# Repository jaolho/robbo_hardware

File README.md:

# CLONE THE REPOSITORY BY CLICKING THE CLONE BUTTON IN THE UPPER RIGHT SIDE OF THE PAGE - THE ONE WITH A DOWN ARROW. #

# README #

This README would normally document whatever steps are necessary to get your application up and running.

### What is this repository for? ###

* Quick summary
* Version
* [Learn Markdown](https://bitbucket.org/tutorials/markdowndemo)

### How do I get set up? ###

* Summary of set up
* Configuration
* Dependencies
* Database configuration
* How to run tests
* Deployment instructions

### Contribution guidelines ###

* Writing tests
* Code review
* Other guidelines

### Who do I talk to? ###

* Repo owner or admin
* Other community or team contact

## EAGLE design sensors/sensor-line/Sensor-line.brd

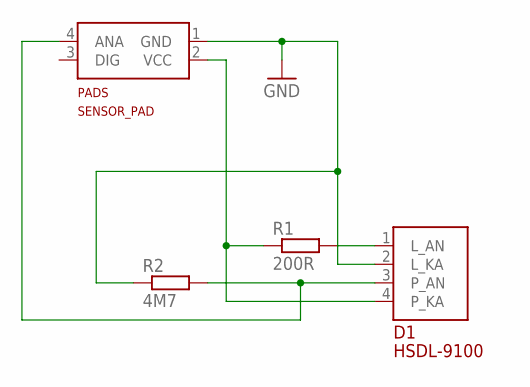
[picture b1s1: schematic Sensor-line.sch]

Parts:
D1: HSDL-9100; MPN HSDL-9100-021
PADS: SENSOR_PAD
R1: 200R; R1206; MPN ERJ8ENF2000V
R2: 4M7; R0805; MPN ASC0805-4M7FT5

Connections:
GND: D1.2 (L_KA), PADS.1 (GND), R2.1
unnamed: D1.1 (L_AN), R1.2
unnamed: D1.3 (P_AN), PADS.4 (ANA), R2.2
unnamed: D1.4 (P_KA), PADS.2 (VCC), R1.1

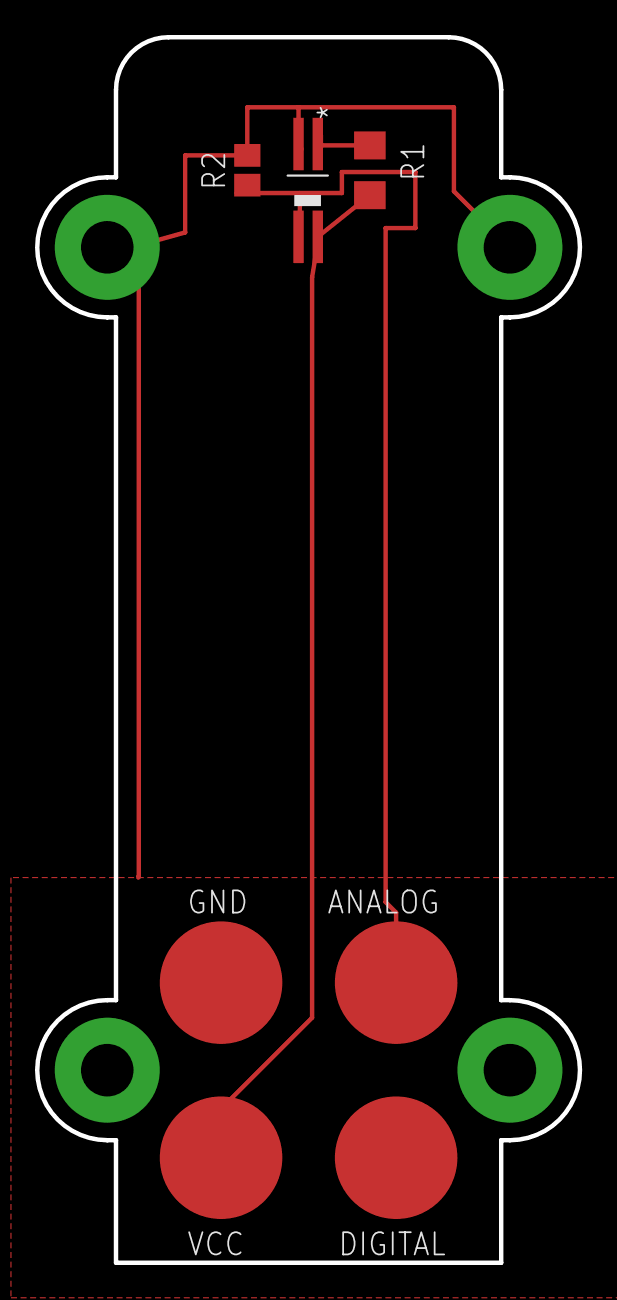
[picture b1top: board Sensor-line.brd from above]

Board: 2 copper layers, 31.0 x 70.0 mm, 4 parts (1 on the bottom side), 4 nets.

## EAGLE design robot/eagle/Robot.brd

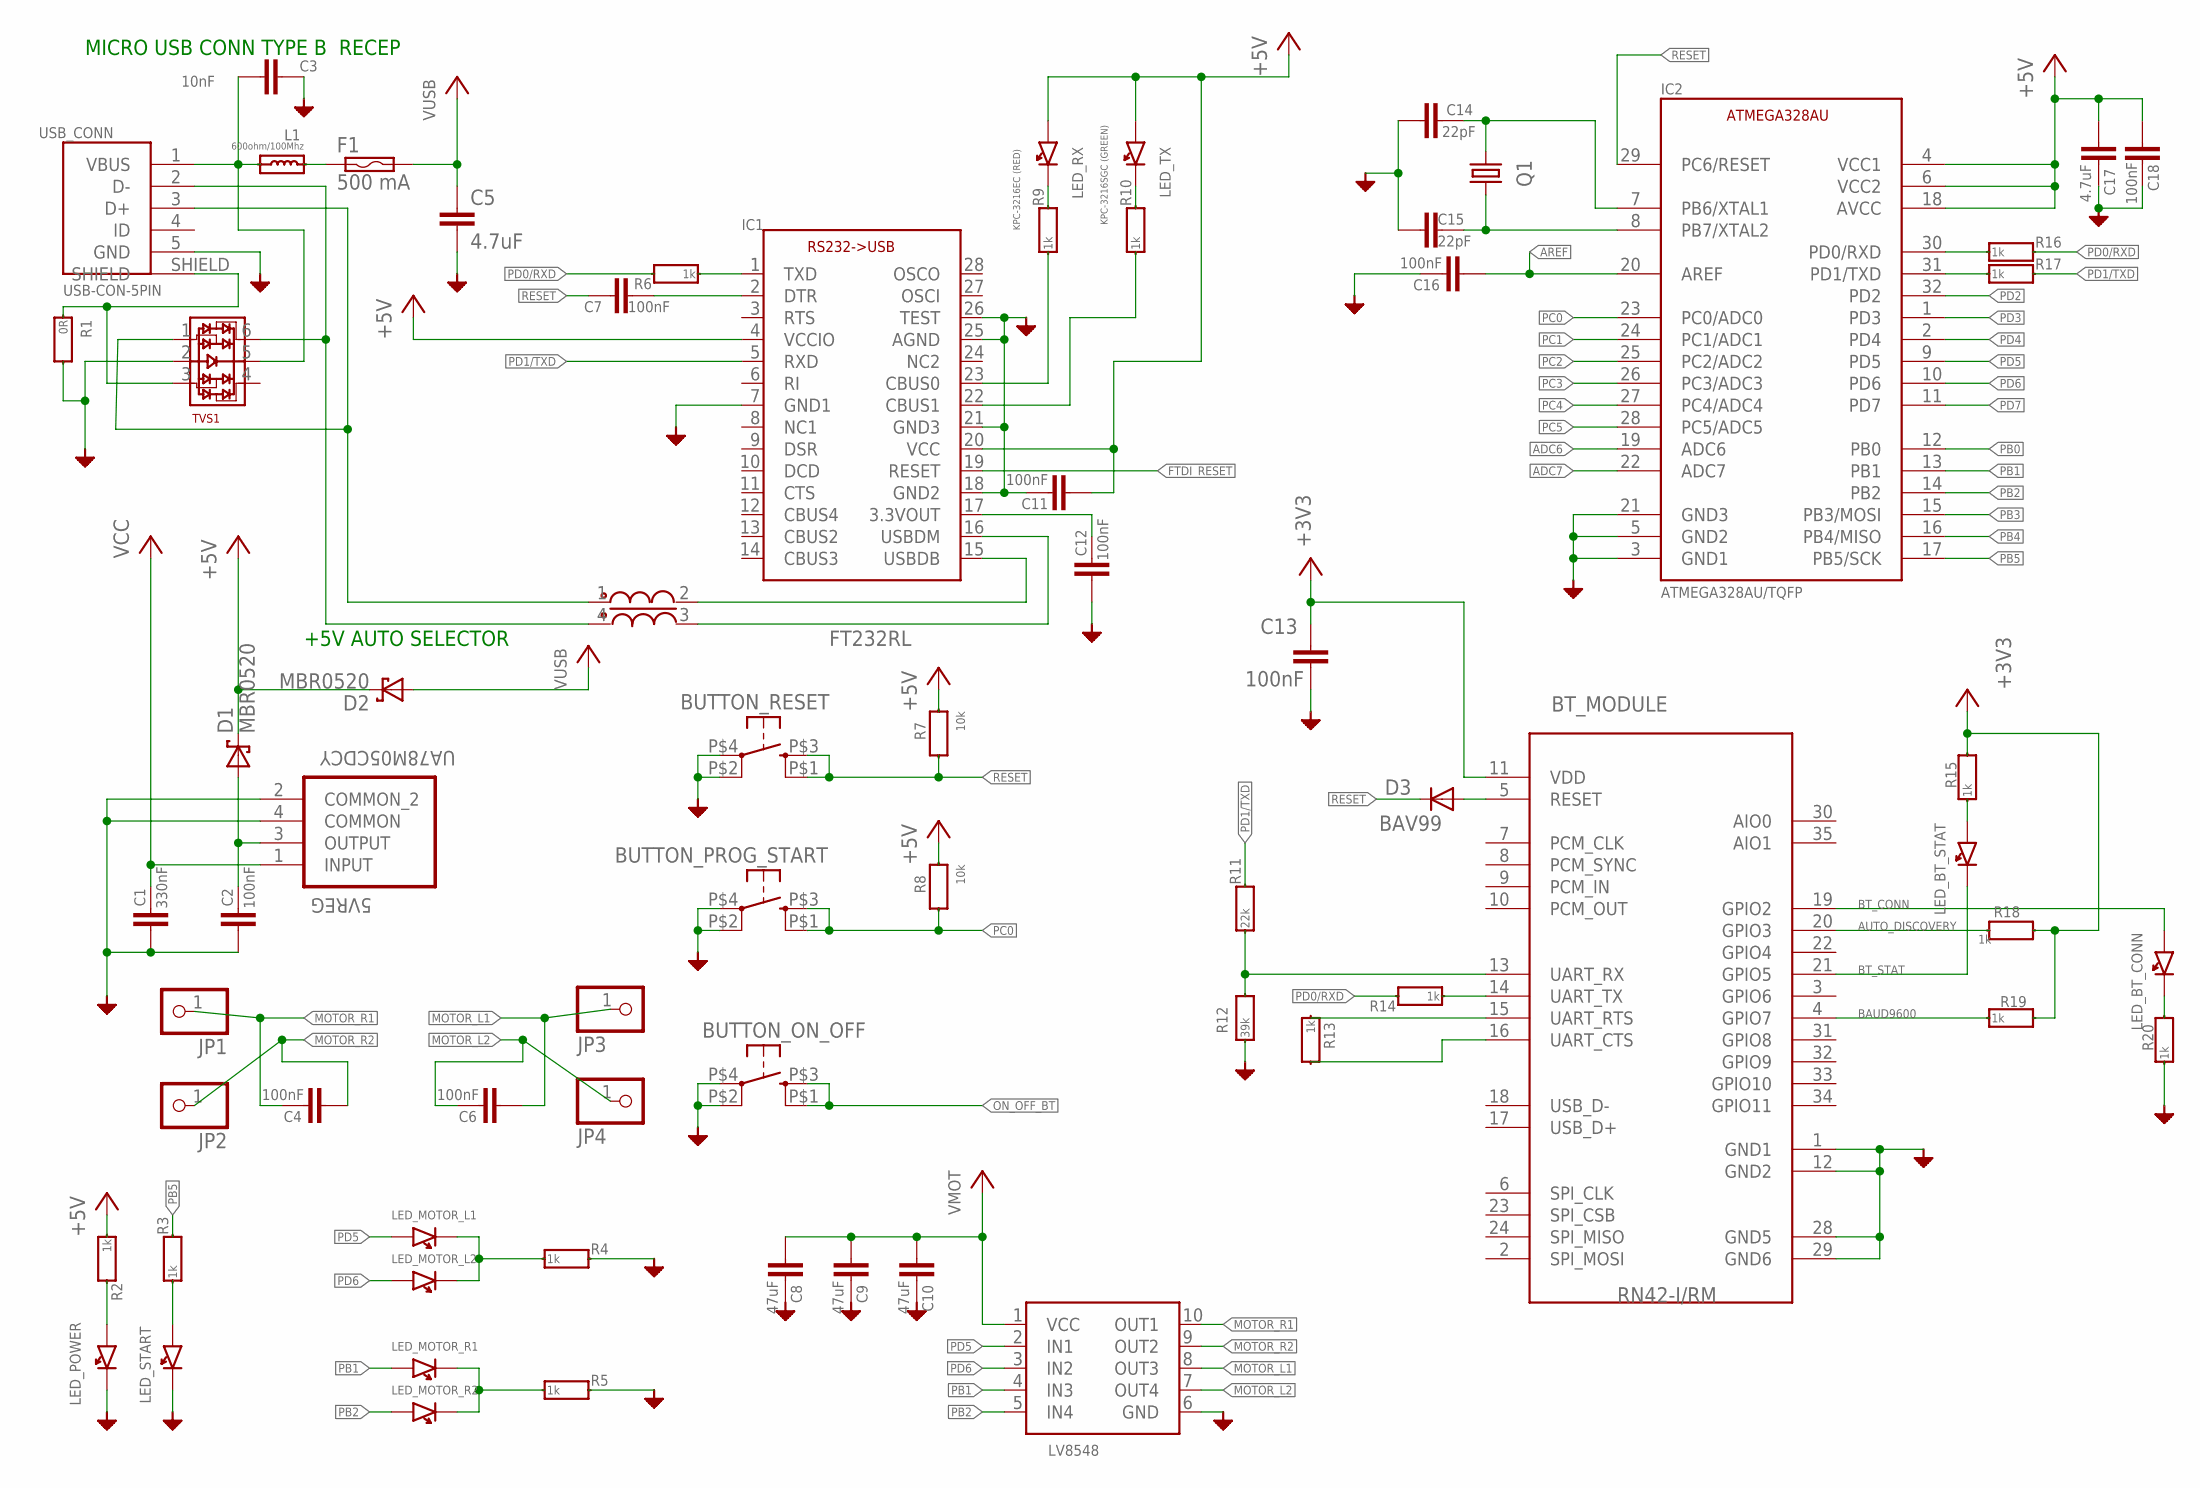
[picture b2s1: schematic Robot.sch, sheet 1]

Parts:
5VREG: UA78M05CDCY; SOT230P700X180-4N
BT_MODULE: RN42-I/RM; RN42; MPN RN42-I/RM
BUTTON_ON_OFF: KSC921J; TACT_SWITCH_4_PIN; MPN KSC921J LFS
BUTTON_PROG_START: KSC921J; TACT_SWITCH_4_PIN; MPN KSC921J LFS
BUTTON_RESET: KSC921J; TACT_SWITCH_4_PIN; MPN KSC921J LFS
C1: 330nF; C0805; MPN 08053C334KAT2A
C2, C4, C6, C7, C11, C12, C13, C16, C18: 100nF; C0805; MPN 08055C104KAT2A
C3: 10nF; C0805; MPN MC0805B103K500CT
C5, C17: 4.7uF; C0805; MPN GRM21BR61E475KA12L
C8, C9, C10: 47uF; C1210; MPN GRM32EC81C476KE15L
C14, C15: 22pF; C0805; MPN CC0805JRNPO9BN220
D1, D2: MBR0520; SOD123; MPN MBR0520L
D3: BAV99; SOT23; MPN BAV99
F1: 500 mA; PT1206; MPN NANOSMDC050F/13.2-2
IC1: FT232RL; SSOP28; MPN FT232RL-REEL
IC2: ATMEGA328AU/TQFP; TQFP32-08; MPN ATMEGA328P-AU
JP1, JP2, JP3, JP4: 1X01 PIN; 1X01; MPN 61300111121
L1: 600ohm/100Mhz; R0603; MPN 742792651
LED_BT_CONN: KPC-3216SGC; LED3216_PAC; MPN KPC-3216SGC
LED_BT_STAT: KPC-3216SGC; LED3216_PAC; MPN KPC-3216SGC
LED_MOTOR_L1: APT3216QBC/D (BLUE); LED3216_PAC; MOUSER_PART_NO 604-APT3216QBC/D
LED_MOTOR_L2: KPC-3216YC; LED3216_PAC; MPN KPC-3216YC
LED_MOTOR_R1: APT3216QBC/D (BLUE); LED3216_PAC; MOUSER_PART_NO 604-APT3216QBC/D
LED_MOTOR_R2: KPC-3216YC; LED3216_PAC; MPN KPC-3216YC
LED_POWER: KPC-3216SGC (GREEN); LED3216_PAC; MPN KPC-3216SGC
LED_RX: KPC-3216EC (RED); LED3216_PAC; MPN KPC-3216EC
LED_START: KPC-3216SGC; LED3216_PAC; MPN KPC-3216SGC
LED_TX: KPC-3216SGC (GREEN); LED3216_PAC; MPN KPC-3216SGC
MOTOR_CONTROLLER: LV8548; MPN LV8548MC-AH
Q1: 16MHz; SM49; MPN LFXTAL003237
R1: 0R; R0805; MPN MC01W08050R
R2, R3, R4, R5, R6, R9, R10, R13, R14, R15, R16, R17, R18, R19, R20: 1k; R0805; MPN CRCW08051K00FKTA
R7, R8: 10k; R0805; MPN RC0805FR-0710KL
R11: 22k; R0805; MPN WCR0805-22KFI
R12: 39k; R0805; MPN WCR0805-39KFI
TVS1: PRTR5V0U4Y; SOT363; MPN PRTR5V0U4Y,125
USB_CONN: USB-CON-5PIN; USB-MICRO-MOLEX-105017-0001_V2; MPN 105017-0001
USB_FILTER: SRF3216A; MPN SRF3216A-900Y

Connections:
+3V3: BT_MODULE.11 (VDD), C13.1, R15.2, R18.2, R19.2; also elsewhere on the board
+5V: C11.2, C17.2, C18.2, D1.1 (K), D2.1 (K), IC1.4 (VCCIO), IC1.20 (VCC), IC2.4 (VCC1), IC2.6 (VCC2), IC2.18 (AVCC), LED_RX.1, LED_TX.1, R2.1, R7.2, R8.2; also elsewhere on the board
ADC6: IC2.19 (ADC6); also elsewhere on the board
ADC7: IC2.22 (ADC7); also elsewhere on the board
AREF: C16.2, IC2.20 (AREF); also elsewhere on the board
AUTO_DISCOVERY: BT_MODULE.20 (GPIO3), R18.1
BAUD9600: BT_MODULE.4 (GPIO7), R19.1
BT_CONN: BT_MODULE.19 (GPIO2), LED_BT_CONN.1
BT_STAT: BT_MODULE.21 (GPIO5), LED_BT_STAT.2
FTDI_RESET: IC1.19 (RESET); also elsewhere on the board
GND: 5VREG.2 (COMMON_2), 5VREG.4 (COMMON), BT_MODULE.1 (GND1), BT_MODULE.12 (GND2), BT_MODULE.28 (GND5), BT_MODULE.29 (GND6), BUTTON_ON_OFF.P$2 (2), BUTTON_ON_OFF.P$4 (1), BUTTON_PROG_START.P$2 (2), BUTTON_PROG_START.P$4 (1), BUTTON_RESET.P$2 (2), BUTTON_RESET.P$4 (1), C1.2, C2.2, C3.1, C5.2, C8.1, C9.1, C10.1, C11.1, C12.2, C13.2, C14.2, C15.2, C16.1, C17.1, C18.1, IC1.7 (GND1), IC1.18 (GND2), IC1.21 (GND3), IC1.25 (AGND), IC1.26 (TEST), IC2.3 (GND1), IC2.5 (GND2), IC2.21 (GND3), LED_POWER.2, LED_START.2, MOTOR_CONTROLLER.6 (GND), R1.2, R4.2, R5.2, R12.1, R20.1, TVS1.2, USB_CONN.5 (GND); also elsewhere on the board
MOTOR_L1: C6.2, JP3.1, MOTOR_CONTROLLER.8 (OUT3)
MOTOR_L2: C6.1, JP4.1, MOTOR_CONTROLLER.7 (OUT4)
MOTOR_L_ON: LED_MOTOR_L1.2, LED_MOTOR_L2.2, R4.1
MOTOR_R1: C4.1, JP1.1, MOTOR_CONTROLLER.10 (OUT1)
MOTOR_R2: C4.2, JP2.1, MOTOR_CONTROLLER.9 (OUT2)
MOTOR_R_ON: LED_MOTOR_R1.2, LED_MOTOR_R2.2, R5.1
unnamed: BT_MODULE.5 (RESET), D3.1 (A)
unnamed: IC1.1 (TXD), R6.1
unnamed: LED_START.1, R3.1
unnamed: BT_MODULE.14 (UART_TX), R14.1
unnamed: BT_MODULE.15 (UART_RTS), R13.1
unnamed: BT_MODULE.16 (UART_CTS), R13.2
unnamed: IC1.15 (USBDB), USB_FILTER.2
unnamed: LED_BT_STAT.1, R15.1
unnamed: LED_BT_CONN.2, R20.2
unnamed: IC1.16 (USBDM), USB_FILTER.3
unnamed: BT_MODULE.13 (UART_RX), R11.1, R12.2
unnamed: F1.1A (1), F1.1B (1), L1.1
unnamed: 5VREG.3 (OUTPUT), C2.1, D1.2 (A)
unnamed: C12.1, IC1.17 (3.3VOUT)
unnamed: C15.1, IC2.8 (PB7/XTAL2), Q1.2
unnamed: C14.1, IC2.7 (PB6/XTAL1), Q1.1
unnamed: TVS1.1, USB_CONN.3 (D+), USB_FILTER.1
unnamed: TVS1.6, USB_CONN.2 (D-), USB_FILTER.4
unnamed: C7.1, IC1.2 (DTR)
unnamed: C3.2, L1.2, TVS1.5, USB_CONN.1 (VBUS)
unnamed: IC1.23 (CBUS0), R9.1
unnamed: LED_RX.2, R9.2
unnamed: LED_TX.2, R10.2
unnamed: IC1.22 (CBUS1), R10.1
unnamed: LED_POWER.1, R2.2
unnamed: IC2.30 (PD0/RXD), R16.1
unnamed: IC2.31 (PD1/TXD), R17.1
ON_OFF_BT: BUTTON_ON_OFF.P$1 (4), BUTTON_ON_OFF.P$3 (3); also elsewhere on the board
PB0: IC2.12 (PB0); also elsewhere on the board
PB1: IC2.13 (PB1), LED_MOTOR_R1.1, MOTOR_CONTROLLER.4 (IN3); also elsewhere on the board
PB2: IC2.14 (PB2), LED_MOTOR_R2.1, MOTOR_CONTROLLER.5 (IN4)
PB3: IC2.15 (PB3/MOSI); also elsewhere on the board
PB4: IC2.16 (PB4/MISO); also elsewhere on the board
PB5: IC2.17 (PB5/SCK), R3.2; also elsewhere on the board
PC0: BUTTON_PROG_START.P$1 (4), BUTTON_PROG_START.P$3 (3), IC2.23 (PC0/ADC0), R8.1; also elsewhere on the board
PC1: IC2.24 (PC1/ADC1); also elsewhere on the board
PC2: IC2.25 (PC2/ADC2); also elsewhere on the board
PC3: IC2.26 (PC3/ADC3); also elsewhere on the board
PC4: IC2.27 (PC4/ADC4); also elsewhere on the board
PC5: IC2.28 (PC5/ADC5); also elsewhere on the board
PD0/RXD: R6.2, R14.2, R16.2
PD1/TXD: IC1.5 (RXD), R11.2, R17.2
PD2: IC2.32 (PD2); also elsewhere on the board
PD3: IC2.1 (PD3); also elsewhere on the board
PD4: IC2.2 (PD4); also elsewhere on the board
PD5: IC2.9 (PD5), LED_MOTOR_L1.1, MOTOR_CONTROLLER.2 (IN1); also elsewhere on the board
PD6: IC2.10 (PD6), LED_MOTOR_L2.1, MOTOR_CONTROLLER.3 (IN2)
PD7: IC2.11 (PD7); also elsewhere on the board
RESET: BUTTON_RESET.P$1 (4), BUTTON_RESET.P$3 (3), C7.2, D3.3 (C), IC2.29 (PC6/RESET), R7.1; also elsewhere on the board
SHIELD: R1.1, TVS1.3, USB_CONN.SHIELD
USB_VCC: C5.1, D2.2 (A), F1.2A (2), F1.2B (2); also elsewhere on the board
VCC: 5VREG.1 (INPUT), C1.1; also elsewhere on the board
VMOT: C8.2, C9.2, C10.2, MOTOR_CONTROLLER.1 (VCC); also elsewhere on the board

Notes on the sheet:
MICRO USB CONN TYPE B RECEP
+5V AUTO SELECTOR

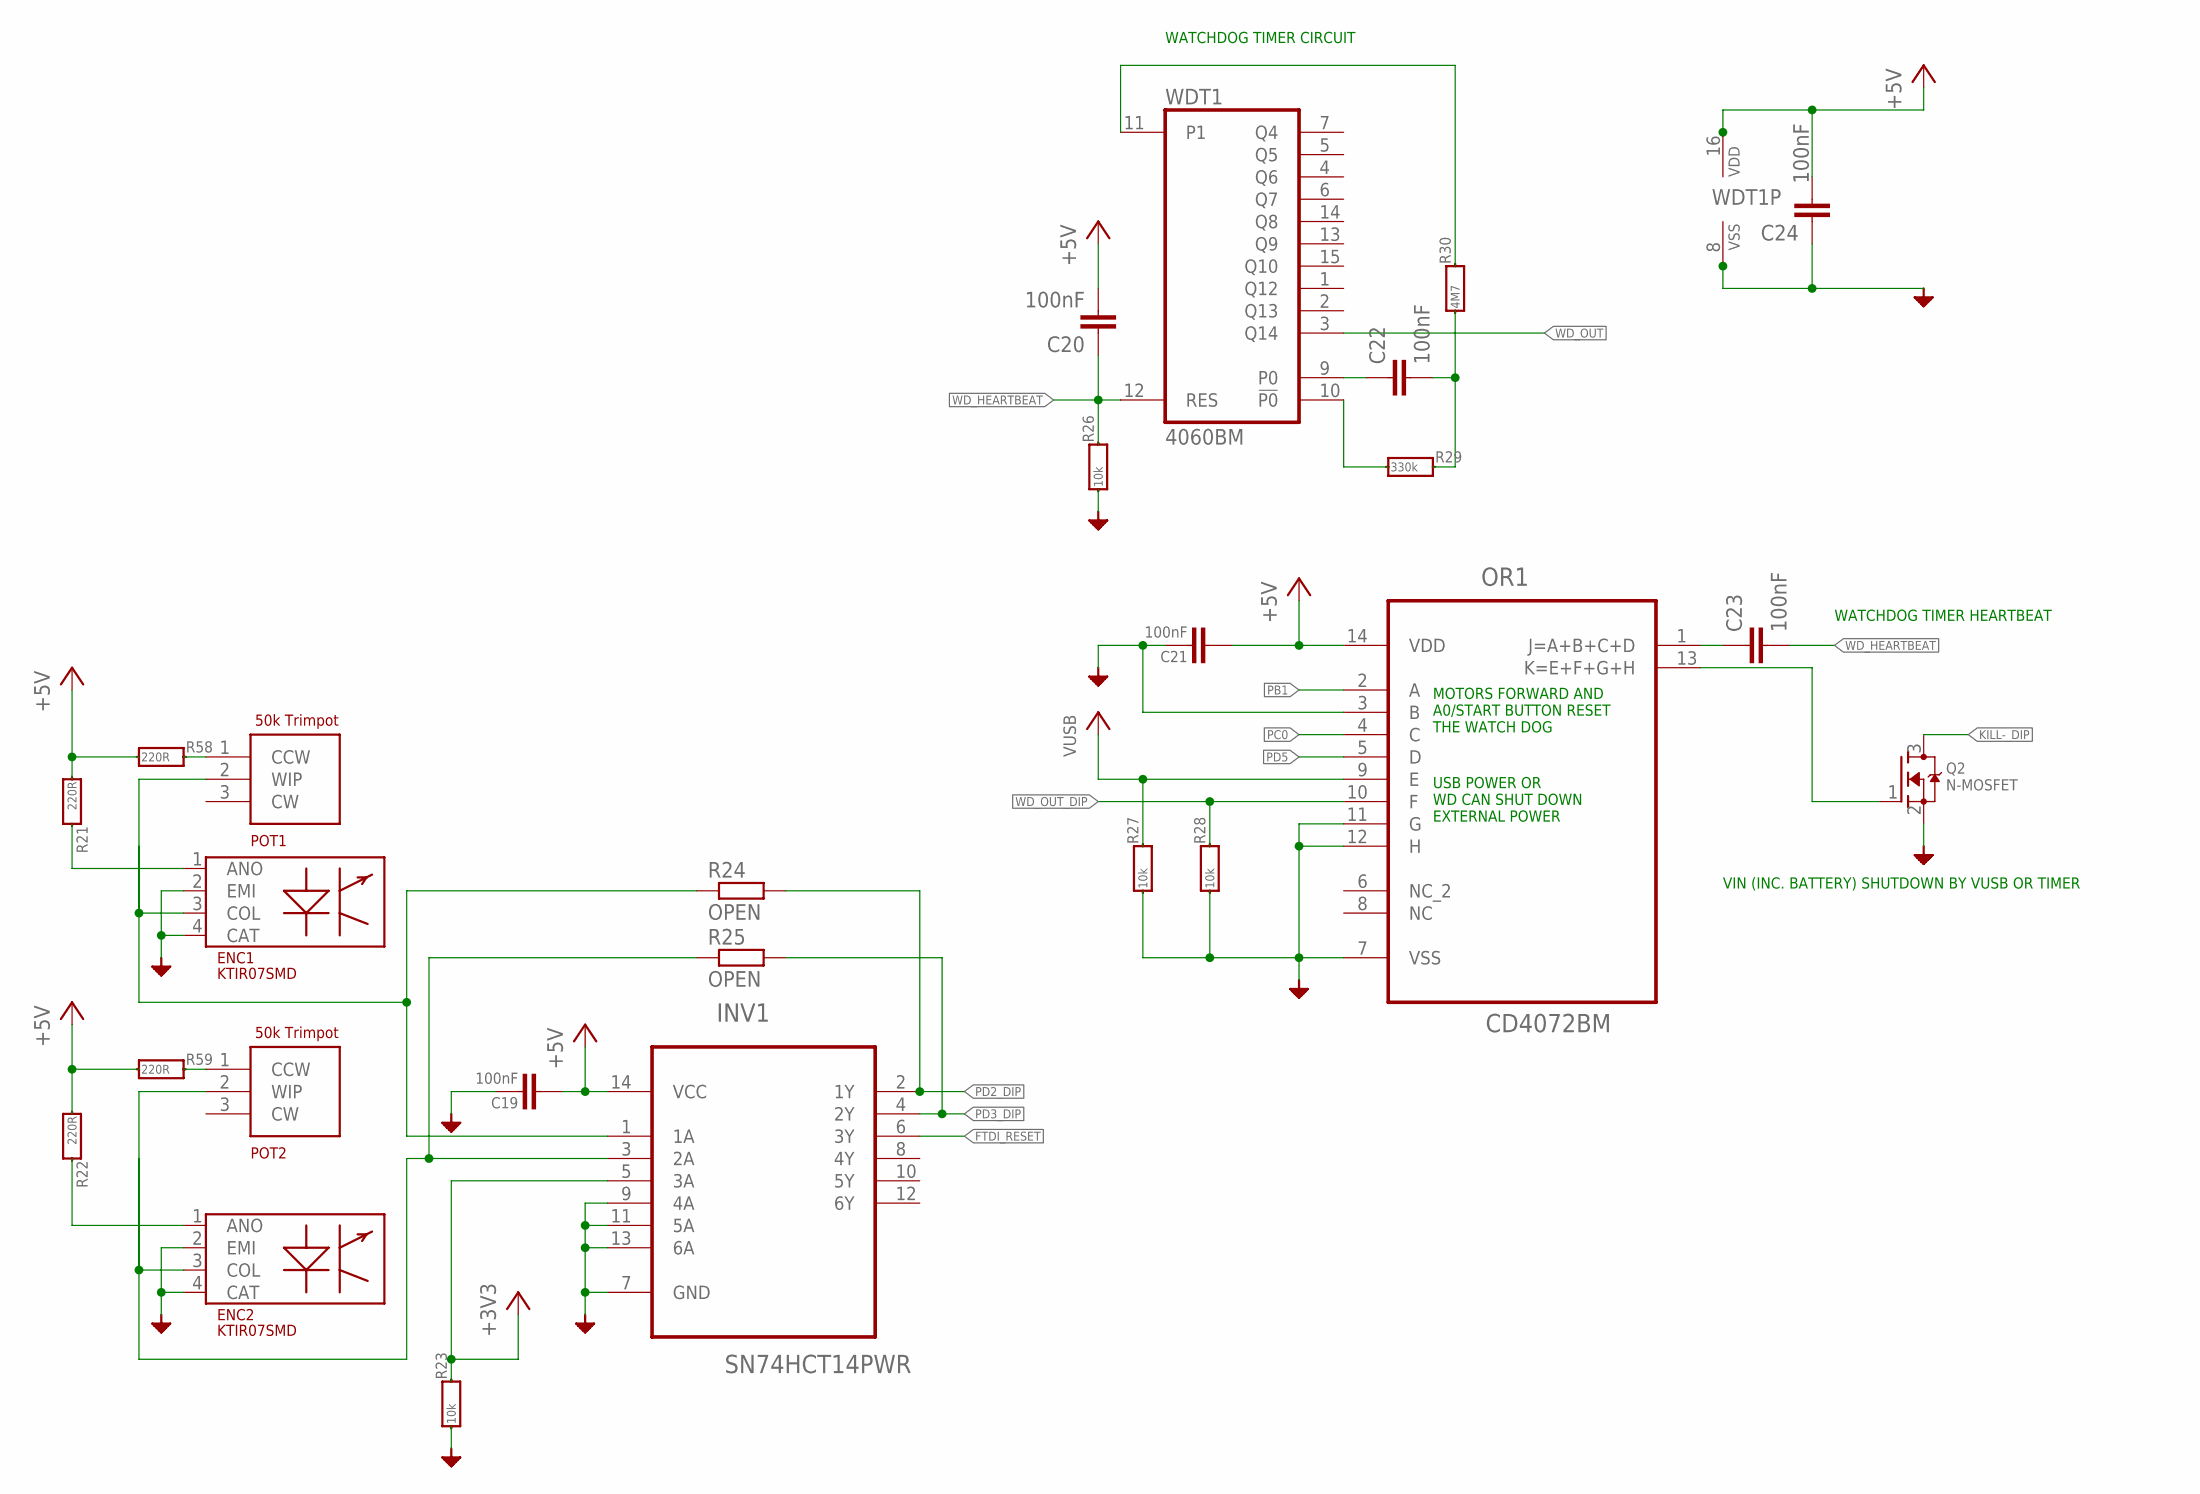
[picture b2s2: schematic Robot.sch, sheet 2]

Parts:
C19, C20, C21, C22, C23, C24: 100nF; C0805; MPN 08055C104KAT2A
ENC1, ENC2: KTIR07SMD; KTIR07; MPN KTIR0711S
INV1: SN74HCT14PWR; SOP65P640X120-14N; MPN 74HCT14PW,118
OR1: CD4072BM; SOIC127P600X175-14N
POT1, POT2: TC33-TRIMPOT; MPN TC33X-2-503E
Q2: N-MOSFET; SOT23; MPN FDV301N
R21, R22, R58, R59: 220R; R0805; MPN MCWR08X2200FTL
R23, R26, R27, R28: 10k; R0805; MPN RC0805FR-0710KL
R24, R25: OPEN; R0805
R29: 330k; R0805; MPN CRCW0805330KFKEA
R30: 4M7; R0805; MPN RCV08054M70FKEA
WDT1: 4060BM; SO16; MPN CD4060BM

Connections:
+3V3: INV1.5 (3A), R23.2; also elsewhere on the board
+5V: C19.2, C20.2, C21.2, C24.2, INV1.14 (VCC), OR1.14 (VDD), R21.1, R22.1, R58.1, R59.1, WDT1.16 (VDD); also elsewhere on the board
FTDI_RESET: INV1.6 (3Y); also elsewhere on the board
GND: C19.1, C21.1, C24.1, ENC1.2 (EMI), ENC1.4 (CAT), ENC2.2 (EMI), ENC2.4 (CAT), INV1.7 (GND), INV1.9 (4A), INV1.11 (5A), INV1.13 (6A), OR1.3 (B), OR1.7 (VSS), OR1.11 (G), OR1.12 (H), Q2.2 (S), R23.1, R26.1, R27.1, R28.1, WDT1.8 (VSS); also elsewhere on the board
KILL-_DIP: Q2.3 (D); also elsewhere on the board
unnamed: C23.1, OR1.1 (J=A+B+C+D)
unnamed: ENC1.1 (ANO), R21.2
unnamed: ENC2.1 (ANO), R22.2
unnamed: ENC2.3 (COL), INV1.3 (2A), POT2.2 (WIP), R25.1
unnamed: R29.1, WDT1.10 (!P0)
unnamed: ENC1.3 (COL), INV1.1 (1A), POT1.2 (WIP), R24.1
unnamed: C22.1, WDT1.9 (P0)
unnamed: POT2.1 (CCW), R59.2
unnamed: R30.2, WDT1.11 (P1)
unnamed: POT1.1 (CCW), R58.2
unnamed: C22.2, R29.2, R30.1
PB1: OR1.2 (A); also elsewhere on the board
PC0: OR1.4 (C); also elsewhere on the board
PD2_DIP: INV1.2 (1Y), R24.2; also elsewhere on the board
PD3_DIP: INV1.4 (2Y), R25.2; also elsewhere on the board
PD5: OR1.5 (D); also elsewhere on the board
USB/WD_KILL-: OR1.13 (K=E+F+G+H), Q2.1 (G)
USB_VCC: OR1.9 (E), R27.2; also elsewhere on the board
WD_HEARTBEAT: C20.1, C23.2, R26.2, WDT1.12 (RES)
WD_OUT: WDT1.3 (Q14); also elsewhere on the board
WD_OUT_DIP: OR1.10 (F), R28.2; also elsewhere on the board

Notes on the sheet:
WATCHDOG TIMER CIRCUIT
WATCHDOG TIMER HEARTBEAT
VIN (INC. BATTERY) SHUTDOWN BY VUSB OR TIMER
MOTORS FORWARD AND A0/START BUTTON RESET THE WATCH DOG
USB POWER OR WD CAN SHUT DOWN EXTERNAL POWER

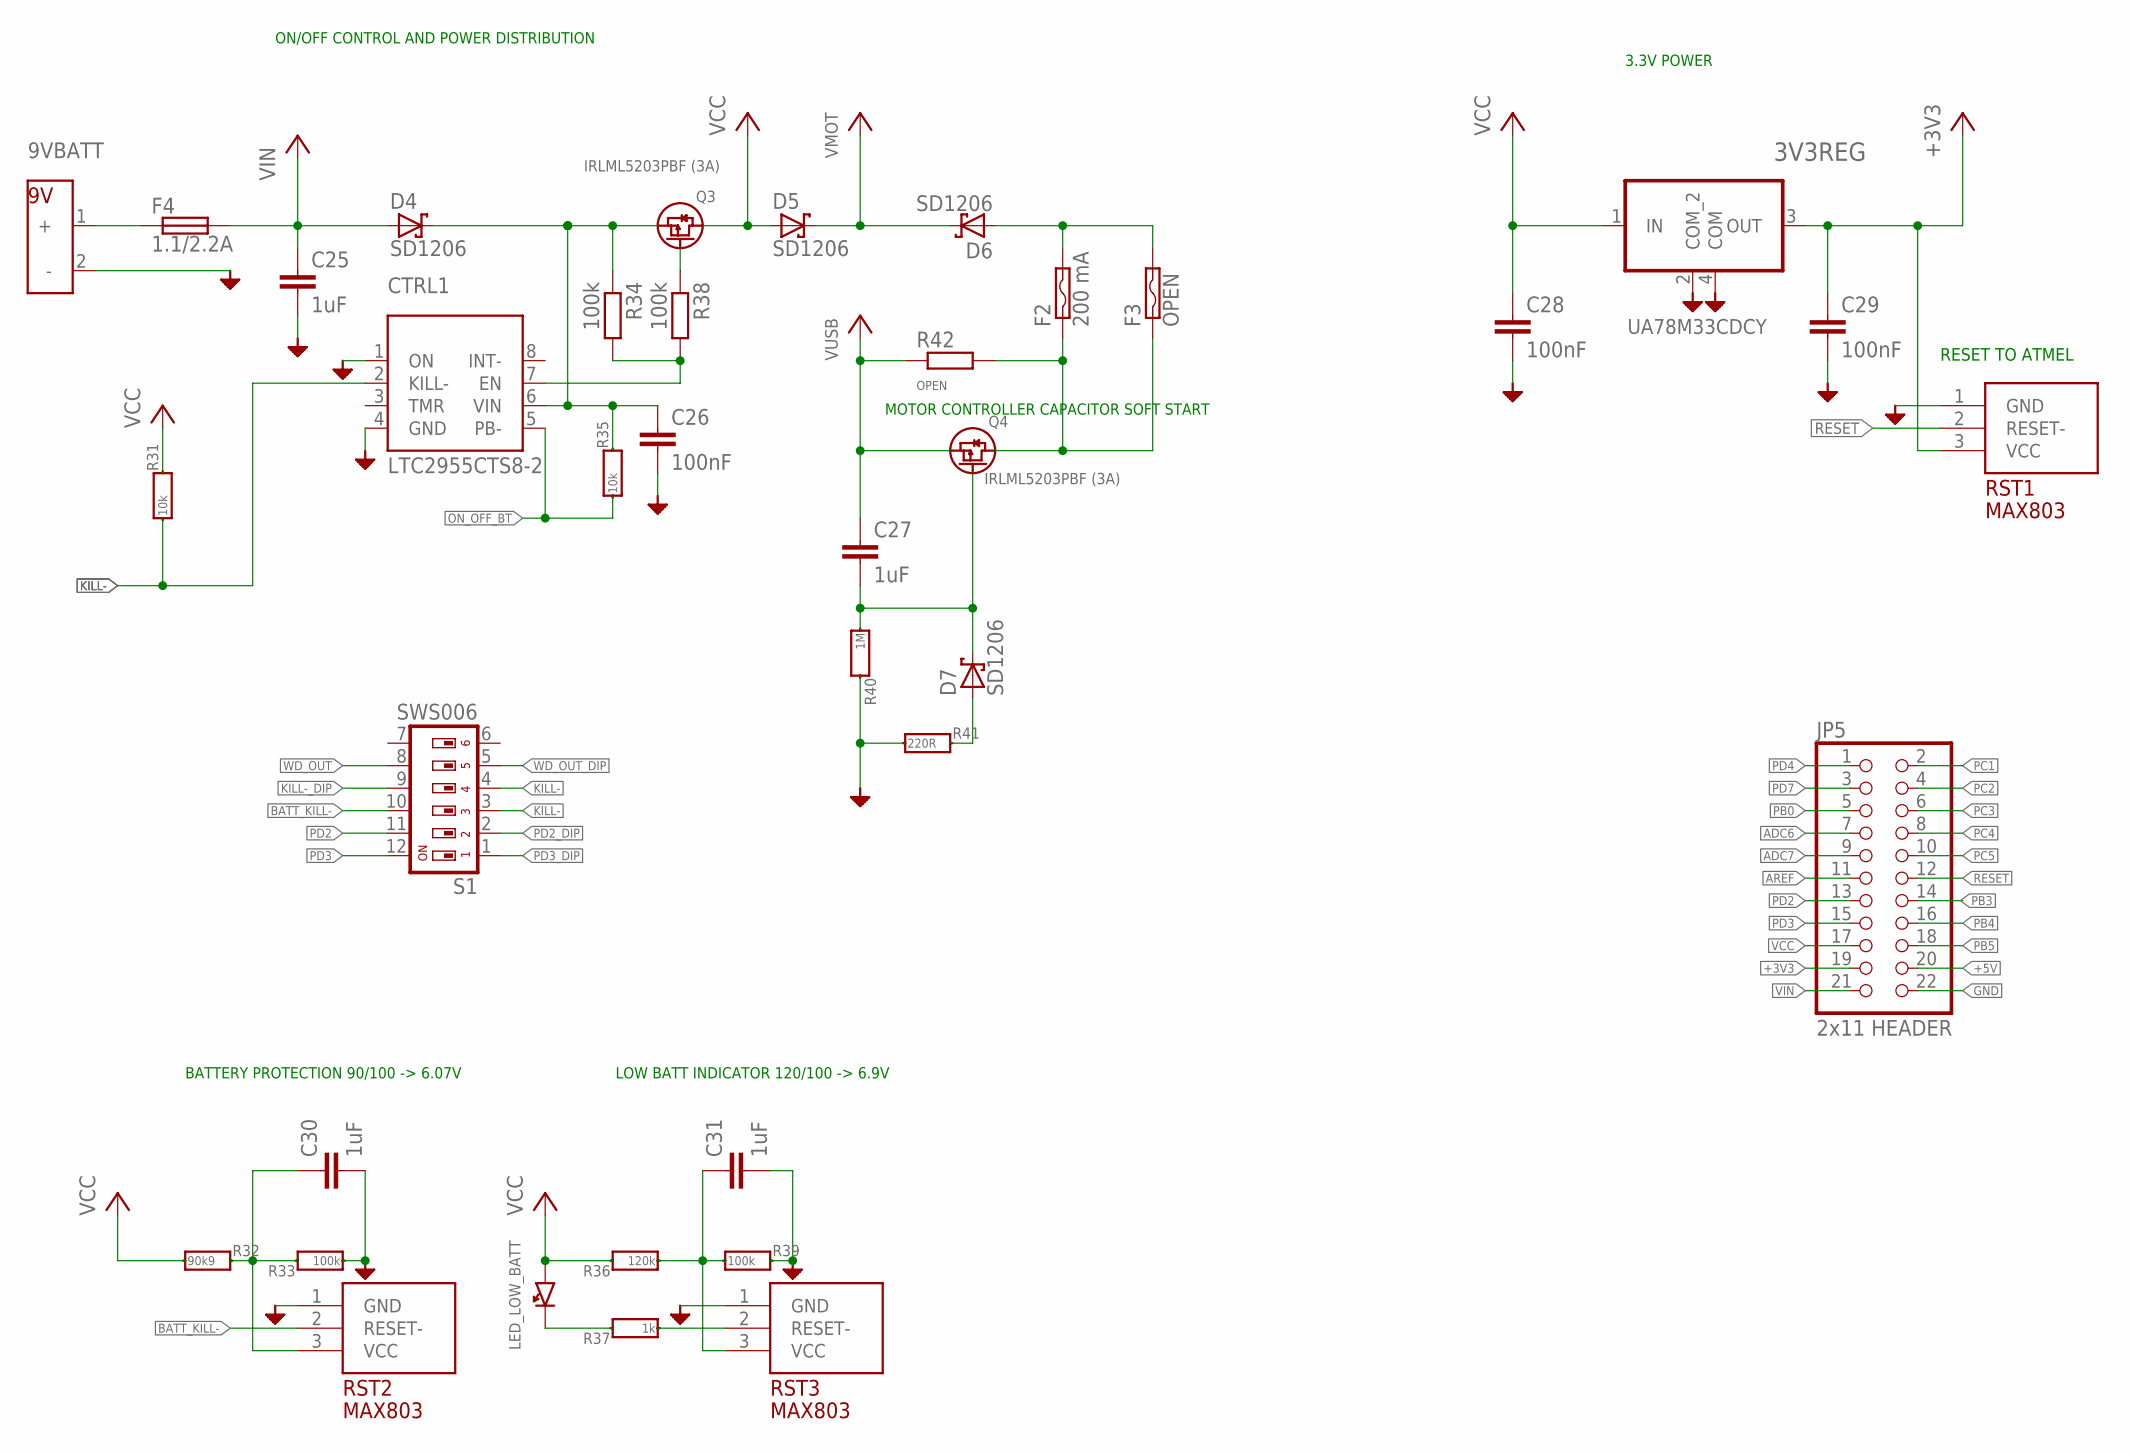
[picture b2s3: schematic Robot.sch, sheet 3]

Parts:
3V3REG: UA78M33CDCY; SOT230P700X180-4N
9VBATT: BATTERY_9V; BATTERY_PAC; MPN 967
C25, C27, C30, C31: 1uF; C0805; MPN 0805B104K500CT
C26, C28, C29: 100nF; C0805; MPN 08055C104KAT2A
CTRL1: LTC2955CTS8-2; 8TSOT23; MPN LTC2955CTS8-2#TRMPBF
D4, D5, D6, D7: SD1206; MPN SD1206S040S2R0
F2: 200 mA; PT1206; MPN NANOSMDC020F-2
F3: OPEN; PT1206
F4: 1.1/2.2A; C1812; MPN MINISMDC110F/16-2; FARNELL 2473642
JP5: 2x11 HEADER; 2X11; MPN 2214S-22SG-85
LED_LOW_BATT: KPC-3216EC (RED); LED3216_PAC; MPN KPC-3216EC
Q3, Q4: IRLML5203PBF (3A); SOT23; MPN IRLML5203PBF
R31, R35: 10k; R0805; MPN RC0805FR-0710KL
R32: 90k9; R0805; MPN MC01W0805190K9
R33, R34, R38, R39: 100k; R0805; MPN RC0805FR-07100KL
R36: 120k; R0805; MPN RC0805FR-07120KL
R37: 1k; R0805; MPN CRCW08051K00FKTA
R40: 1M; R0805; MPN CRCW08051M00FKTB
R41: 220R; R0805; MPN MCWR08X2200FTL
R42: OPEN; R0603
RST1, RST2, RST3: MAX803SC; SC70-3L; MPN MAX803SQ293T1G
S1: SWS006; SMS-006; MPN MCDM(R)-06-T

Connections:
+3V3: 3V3REG.3 (OUT), C29.1, JP5.19, RST1.3 (VCC); also elsewhere on the board
+5V: JP5.20; also elsewhere on the board
ADC6: JP5.7; also elsewhere on the board
ADC7: JP5.9; also elsewhere on the board
AREF: JP5.11; also elsewhere on the board
BATT_KILL-: RST2.2 (RESET-), S1.10
BATT_PROT_ADJ: C30.1, R32.2, R33.2, RST2.3 (VCC)
GND: 3V3REG.2 (COM_2), 3V3REG.4 (COM), 9VBATT.2 (-), C25.2, C26.2, C28.2, C29.2, C30.2, C31.2, CTRL1.1 (ON), CTRL1.4 (GND), JP5.22, R33.1, R39.2, R40.2, R41.1, RST1.1 (GND), RST2.1 (GND), RST3.1 (GND); also elsewhere on the board
KILL-: CTRL1.2 (KILL-), R31.1, S1.3, S1.4
KILL-_DIP: S1.9; also elsewhere on the board
unnamed: Q3.1 (G), R38.1
unnamed: CTRL1.7 (EN), R34.2, R38.2
unnamed: LED_LOW_BATT.2, R37.2
unnamed: D6.ANODE (A), F2.2A (2), F2.2B (2), F3.2A (2), F3.2B (2)
unnamed: R37.1, RST3.2 (RESET-)
unnamed: F2.1A (1), F2.1B (1), F3.1A (1), F3.1B (1), Q4.3 (D), R42.2
unnamed: C27.2, D7.CATHODE (C), Q4.1 (G), R40.1
unnamed: C26.1, CTRL1.6 (VIN), D4.CATHODE (C), Q3.2 (S), R34.1, R35.2
unnamed: D7.ANODE (A), R41.2
unnamed: 9VBATT.1 (+), F4.2
unnamed: C31.1, R36.1, R39.1, RST3.3 (VCC)
ON_OFF_BT: CTRL1.5 (PB-), R35.1; also elsewhere on the board
PB0: JP5.5; also elsewhere on the board
PB3: JP5.14; also elsewhere on the board
PB4: JP5.16; also elsewhere on the board
PB5: JP5.18; also elsewhere on the board
PC1: JP5.2; also elsewhere on the board
PC2: JP5.4; also elsewhere on the board
PC3: JP5.6; also elsewhere on the board
PC4: JP5.8; also elsewhere on the board
PC5: JP5.10; also elsewhere on the board
PD2: JP5.13, S1.11; also elsewhere on the board
PD2_DIP: S1.2; also elsewhere on the board
PD3: JP5.15, S1.12; also elsewhere on the board
PD3_DIP: S1.1; also elsewhere on the board
PD4: JP5.1; also elsewhere on the board
PD7: JP5.3; also elsewhere on the board
RESET: JP5.12, RST1.2 (RESET-); also elsewhere on the board
USB_VCC: C27.1, Q4.2 (S), R42.1; also elsewhere on the board
VCC: 3V3REG.1 (IN), C28.1, D5.ANODE (A), JP5.17, LED_LOW_BATT.1, Q3.3 (D), R31.2, R32.1, R36.2; also elsewhere on the board
VIN: C25.1, D4.ANODE (A), F4.1, JP5.21
VMOT: D5.CATHODE (C), D6.CATHODE (C); also elsewhere on the board
WD_OUT: S1.8; also elsewhere on the board
WD_OUT_DIP: S1.5; also elsewhere on the board

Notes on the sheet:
RESET TO ATMEL
LOW BATT INDICATOR 120/100 -> 6.9V
BATTERY PROTECTION 90/100 -> 6.07V
3.3V POWER
ON/OFF CONTROL AND POWER DISTRIBUTION
MOTOR CONTROLLER CAPACITOR SOFT START

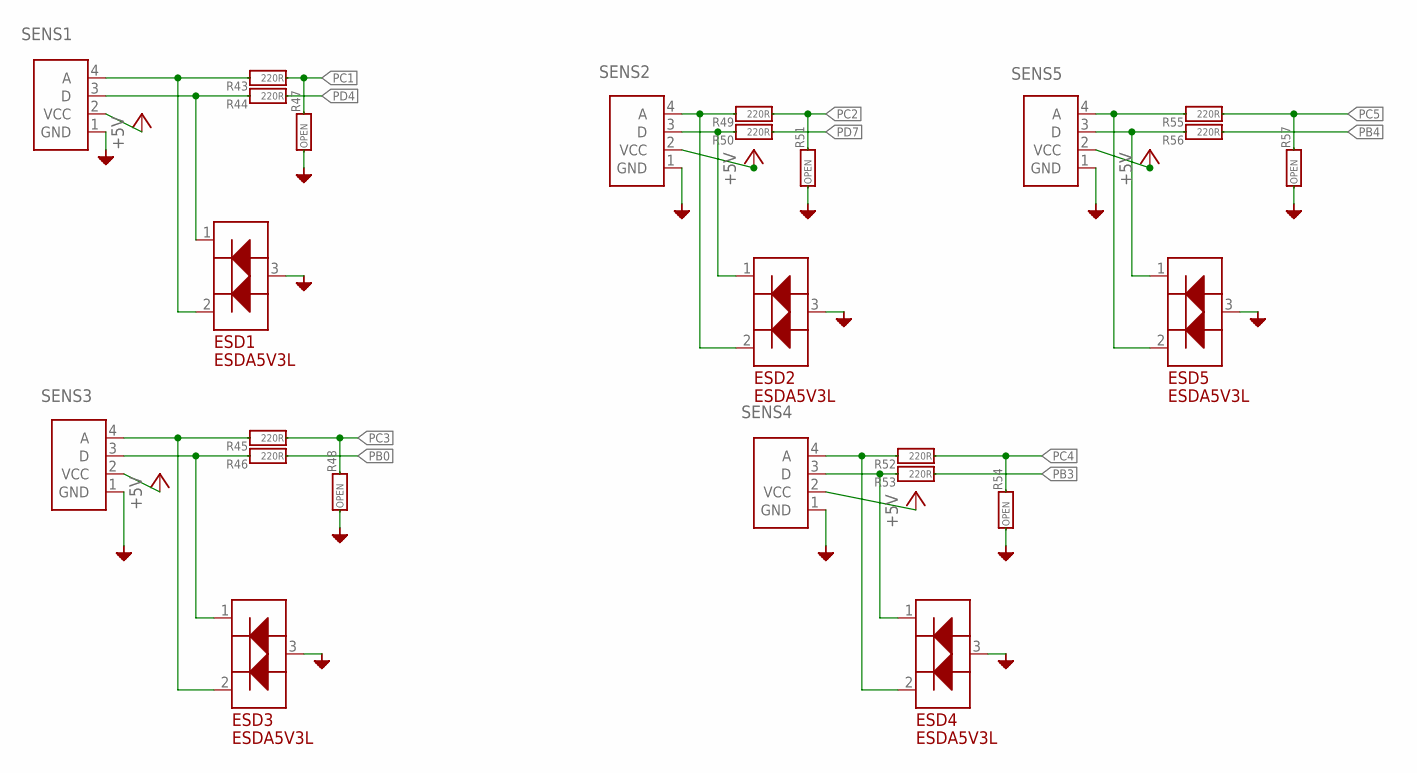
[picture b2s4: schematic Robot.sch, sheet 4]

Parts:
ESD1, ESD2, ESD3, ESD4, ESD5: ESDA5V3L; SOT23; MPN ESDA5V3L
R43, R44, R45, R46, R49, R50, R52, R53, R55, R56: 220R; R0805; MPN MCWR08X2200FTL
R47, R48, R51, R54, R57: OPEN; R0805
SENS1, SENS2, SENS3, SENS4, SENS5: ROBOT_SENSOR

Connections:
+5V: SENS1.2 (VCC), SENS2.2 (VCC), SENS3.2 (VCC), SENS4.2 (VCC), SENS5.2 (VCC); also elsewhere on the board
GND: ESD1.3, ESD2.3, ESD3.3, ESD4.3, ESD5.3, R47.1, R48.1, R51.1, R54.1, R57.1, SENS1.1 (GND), SENS2.1 (GND), SENS3.1 (GND), SENS4.1 (GND), SENS5.1 (GND); also elsewhere on the board
unnamed: ESD4.2, R52.2, SENS4.4 (A)
unnamed: ESD4.1, R53.2, SENS4.3 (D)
unnamed: ESD3.2, R45.2, SENS3.4 (A)
unnamed: ESD1.2, R43.2, SENS1.4 (A)
unnamed: ESD5.2, R55.2, SENS5.4 (A)
unnamed: ESD5.1, R56.2, SENS5.3 (D)
unnamed: ESD2.2, R49.2, SENS2.4 (A)
unnamed: ESD2.1, R50.2, SENS2.3 (D)
unnamed: ESD1.1, R44.2, SENS1.3 (D)
unnamed: ESD3.1, R46.2, SENS3.3 (D)
PB0: R46.1; also elsewhere on the board
PB3: R53.1; also elsewhere on the board
PB4: R56.1; also elsewhere on the board
PC1: R43.1, R47.2; also elsewhere on the board
PC2: R49.1, R51.2; also elsewhere on the board
PC3: R45.1, R48.2; also elsewhere on the board
PC4: R52.1, R54.2; also elsewhere on the board
PC5: R55.1, R57.2; also elsewhere on the board
PD4: R44.1; also elsewhere on the board
PD7: R50.1; also elsewhere on the board

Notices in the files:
parts and their libraries:
SparkFun-DiscreteSemi: Licensing: Creative Commons ShareAlike 4.0 International - https://creativecommons.org/licenses/by-sa/4.0
